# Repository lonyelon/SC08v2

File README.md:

# SC08v2: Simple Computer (8-bits, version 2)

The SC08v2 is a super-simple, **open-hardware 8bit computer** built for retro hardware enthusiasts,
for which a custom default **microcode**, **ISA**, **assembler**, **programming language (based on LISP)**, **compiler** and **operating system** are included.
The design is modular, so any of that can be replaced at any time by the user:

This repository contains various directories and files that help design, build and test both the computer's hardware and it's software. Those files and directories are the following:

| File/Dir     | Explanation                                                                             |
| ------------ | --------------------------------------------------------------------------------------- |
| `assembler/` | converts assembly code to binary data.                                                  |
| `microcode/` | files and scripts that help with designing and building the microcode for the computer. |
| `simulator/` | a complete simulator to test software in.                                               |
| `code/`      | software for the CPU.                                                                   |
| `code/so`    | complete OS.                                                                            |
| `doc/`       | documentation.                                                                          |
| `kicad/`     | KiCAD hardware designs.                                                                 |
| `drawio/`    | DrawIO diagrams.                                                                        |

## Developing software

Check the [programmer's manual](doc/programmers-manual.md) for a detailed guide on how to make software for the CPU.

## Running software in the CPU

To run software in the *simulated* CPU one has two follow two steps: compilation and execution. Let's run one of the test programs for example:

1. Compile the program by running the compiler: `python3 ./comp/compiler.py ./asm/test-programs/mult.asm`. This will result in a file named `result.bin` being created, which can be either flashed into the CPU's ROM or executed by the simulator. Note that the file has a size of exactly 64KB.
2. Run the simulator by entering the `sim` directory and then executing `cargo run ../result.bin | grep -E '^[0-9]+'`. In this case, enter a number (smaller than 255) and press enter. Repeat that step and the product of both will be outputted.

This shows that the simulator needs machine code and can not work with assembly code, since it is a one-to-one digital recreation of the real CPU.

## Contributing

Anything can be added to this repo, in whatever programming language you choose to make it, as long as it is a tool or some documentation for the SC08v2.

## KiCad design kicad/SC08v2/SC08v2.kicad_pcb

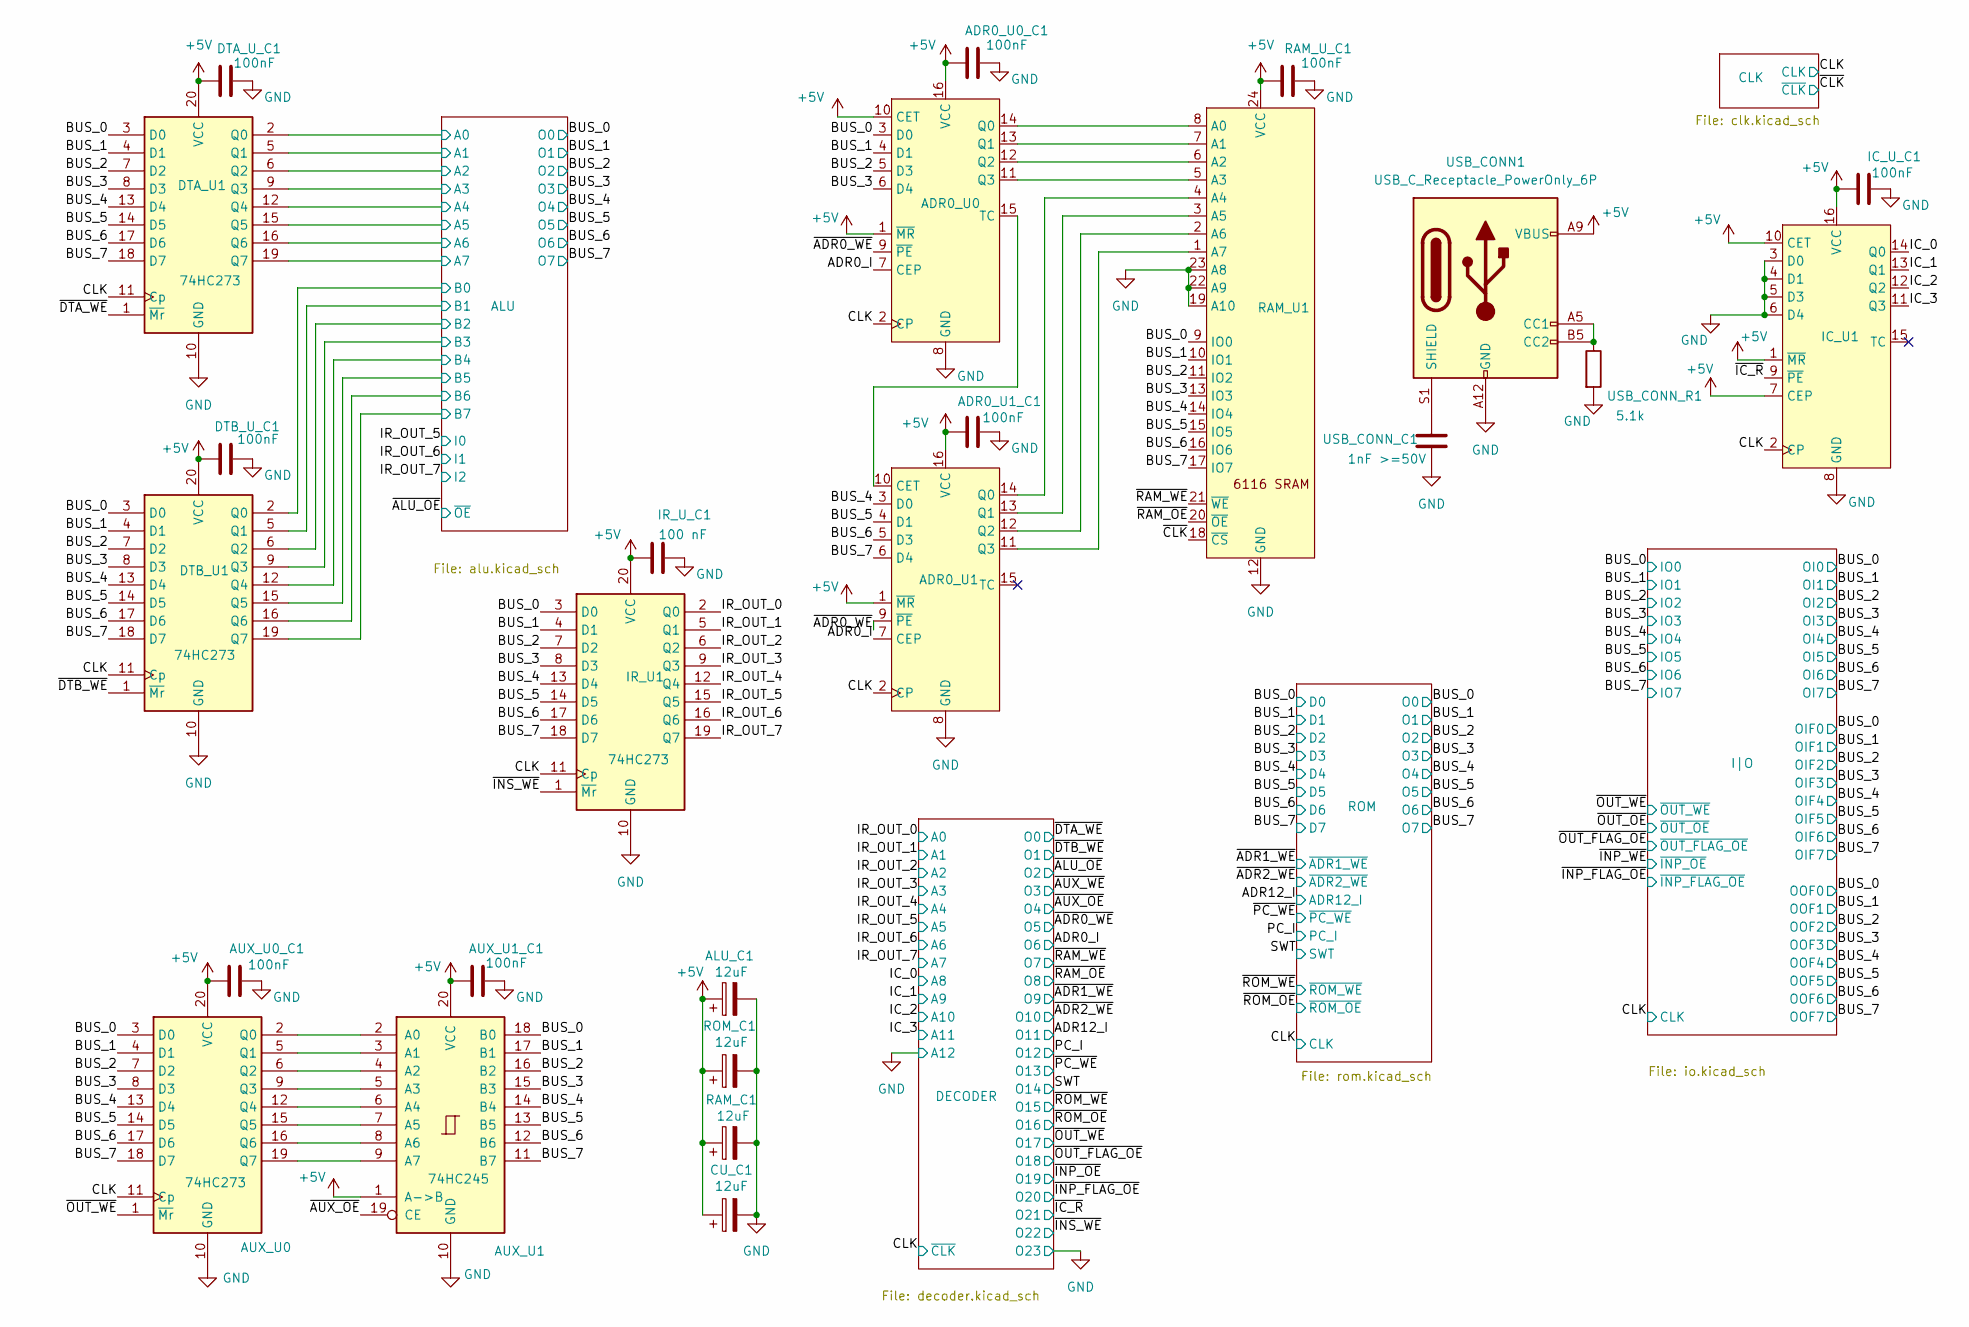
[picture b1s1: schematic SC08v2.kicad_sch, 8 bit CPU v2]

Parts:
ADR0_U0, ADR0_U1: DIP-16_W7.62mm
ADR0_U0_C1, ADR0_U1_C1: 100nF; C_Disc_D3.0mm_W1.6mm_P2.50mm
ALU_C1: 12uF; C_Radial_D5.0mm_H5.0mm_P2.00mm
AUX_U0: 74HC273; DIP-20_W7.62mm
AUX_U0_C1, AUX_U1_C1: 100nF; C_Disc_D3.0mm_W1.6mm_P2.50mm
AUX_U1: 74HC245; DIP-20_W7.62mm
CU_C1: 12uF; C_Radial_D5.0mm_H5.0mm_P2.00mm
DTA_U1: 74HC273; DIP-20_W7.62mm
DTA_U_C1: 100nF; C_Disc_D3.0mm_W1.6mm_P2.50mm
DTB_U1: 74HC273; DIP-20_W7.62mm
DTB_U_C1: 100nF; C_Disc_D3.0mm_W1.6mm_P2.50mm
IC_U1: DIP-16_W7.62mm
IC_U_C1: 100nF; C_Disc_D3.0mm_W1.6mm_P2.50mm
IR_U1: 74HC273; DIP-20_W7.62mm
IR_U_C1: 100 nF; C_Disc_D3.0mm_W1.6mm_P2.50mm
RAM_C1: 12uF; C_Radial_D5.0mm_H5.0mm_P2.00mm
RAM_U1: DIP-24_18.0mmx34.29mm_W15.24mm
RAM_U_C1: 100nF; C_Disc_D3.0mm_W1.6mm_P2.50mm
ROM_C1: 12uF; C_Radial_D5.0mm_H5.0mm_P2.00mm
USB_CONN1: USB_C_Receptacle_PowerOnly_6P; USB_C_Receptacle_GCT_USB4125-xx-x-0190_6P_TopMnt_Horizontal
USB_CONN_C1: 1nF >=50V; C_Disc_D3.0mm_W1.6mm_P2.50mm
USB_CONN_R1: 5.1k; R_Axial_DIN0204_L3.6mm_D1.6mm_P5.08mm_Horizontal

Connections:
+5V: ADR0_U0.1 (~MR), ADR0_U0.10 (CET), ADR0_U0.16 (VCC), ADR0_U0_C1.1, ADR0_U1.1 (~MR), ADR0_U1.16 (VCC), ADR0_U1_C1.1, ALU_C1.1, AUX_U0.20 (VCC), AUX_U0_C1.1, AUX_U1.1 (A->B), AUX_U1.20 (VCC), AUX_U1_C1.1, CU_C1.1, DTA_U1.20 (VCC), DTA_U_C1.1, DTB_U1.20 (VCC), DTB_U_C1.1, IC_U1.1 (~MR), IC_U1.7 (CEP), IC_U1.10 (CET), IC_U1.16 (VCC), IC_U_C1.1, IR_U1.20 (VCC), IR_U_C1.1, RAM_C1.1, RAM_U1.24 (VCC), RAM_U_C1.1, ROM_C1.1, USB_CONN1.A9 (VBUS), USB_CONN1.B9 (VBUS); also elsewhere on the board
/ADR0_I: ADR0_U0.7 (CEP), ADR0_U1.7 (CEP); also elsewhere on the board
/ALU/A0: DTA_U1.2 (Q0); also elsewhere on the board
/ALU/A1: DTA_U1.5 (Q1); also elsewhere on the board
/ALU/A2: DTA_U1.6 (Q2); also elsewhere on the board
/ALU/A3: DTA_U1.9 (Q3); also elsewhere on the board
/ALU/A4: DTA_U1.12 (Q4); also elsewhere on the board
/ALU/A5: DTA_U1.15 (Q5); also elsewhere on the board
/ALU/A6: DTA_U1.16 (Q6); also elsewhere on the board
/ALU/A7: DTA_U1.19 (Q7); also elsewhere on the board
/ALU/B0: DTB_U1.2 (Q0); also elsewhere on the board
/ALU/B1: DTB_U1.5 (Q1); also elsewhere on the board
/ALU/B2: DTB_U1.6 (Q2); also elsewhere on the board
/ALU/B3: DTB_U1.9 (Q3); also elsewhere on the board
/ALU/B4: DTB_U1.12 (Q4); also elsewhere on the board
/ALU/B5: DTB_U1.15 (Q5); also elsewhere on the board
/ALU/B6: DTB_U1.16 (Q6); also elsewhere on the board
/ALU/B7: DTB_U1.19 (Q7); also elsewhere on the board
/BUS_0: ADR0_U0.3 (D0), AUX_U0.3 (D0), AUX_U1.18 (B0), DTA_U1.3 (D0), DTB_U1.3 (D0), IR_U1.3 (D0), RAM_U1.9 (IO0); also elsewhere on the board
/BUS_1: ADR0_U0.4 (D1), AUX_U0.4 (D1), AUX_U1.17 (B1), DTA_U1.4 (D1), DTB_U1.4 (D1), IR_U1.4 (D1), RAM_U1.10 (IO1); also elsewhere on the board
/BUS_2: ADR0_U0.5 (D3), AUX_U0.7 (D2), AUX_U1.16 (B2), DTA_U1.7 (D2), DTB_U1.7 (D2), IR_U1.7 (D2), RAM_U1.11 (IO2); also elsewhere on the board
/BUS_3: ADR0_U0.6 (D4), AUX_U0.8 (D3), AUX_U1.15 (B3), DTA_U1.8 (D3), DTB_U1.8 (D3), IR_U1.8 (D3), RAM_U1.13 (IO3); also elsewhere on the board
/BUS_4: ADR0_U1.3 (D0), AUX_U0.13 (D4), AUX_U1.14 (B4), DTA_U1.13 (D4), DTB_U1.13 (D4), IR_U1.13 (D4), RAM_U1.14 (IO4); also elsewhere on the board
/BUS_5: ADR0_U1.4 (D1), AUX_U0.14 (D5), AUX_U1.13 (B5), DTA_U1.14 (D5), DTB_U1.14 (D5), IR_U1.14 (D5), RAM_U1.15 (IO5); also elsewhere on the board
/BUS_6: ADR0_U1.5 (D3), AUX_U0.17 (D6), AUX_U1.12 (B6), DTA_U1.17 (D6), DTB_U1.17 (D6), IR_U1.17 (D6), RAM_U1.16 (IO6); also elsewhere on the board
/BUS_7: ADR0_U1.6 (D4), AUX_U0.18 (D7), AUX_U1.11 (B7), DTA_U1.18 (D7), DTB_U1.18 (D7), IR_U1.18 (D7), RAM_U1.17 (IO7); also elsewhere on the board
/CLK: ADR0_U0.2 (CP), ADR0_U1.2 (CP), AUX_U0.11 (Cp), DTA_U1.11 (Cp), DTB_U1.11 (Cp), IC_U1.2 (CP), IR_U1.11 (Cp); also elsewhere on the board
/IC_0: IC_U1.14 (Q0); also elsewhere on the board
/IC_1: IC_U1.13 (Q1); also elsewhere on the board
/IC_2: IC_U1.12 (Q2); also elsewhere on the board
/IC_3: IC_U1.11 (Q3); also elsewhere on the board
/IR_OUT_0: IR_U1.2 (Q0); also elsewhere on the board
/IR_OUT_1: IR_U1.5 (Q1); also elsewhere on the board
/IR_OUT_2: IR_U1.6 (Q2); also elsewhere on the board
/IR_OUT_3: IR_U1.9 (Q3); also elsewhere on the board
/IR_OUT_4: IR_U1.12 (Q4); also elsewhere on the board
/IR_OUT_5: IR_U1.15 (Q5); also elsewhere on the board
/IR_OUT_6: IR_U1.16 (Q6); also elsewhere on the board
/IR_OUT_7: IR_U1.19 (Q7); also elsewhere on the board
/~ADR0_WE: ADR0_U0.9 (~PE), ADR0_U1.9 (~PE); also elsewhere on the board
/~AUX_OE: AUX_U1.19 (CE); also elsewhere on the board
/~CLK: RAM_U1.18 (~CS); also elsewhere on the board
/~DTA_WE: DTA_U1.1 (~Mr); also elsewhere on the board
/~DTB_WE: DTB_U1.1 (~Mr); also elsewhere on the board
/~IC_R: IC_U1.9 (~PE); also elsewhere on the board
/~INS_WE: IR_U1.1 (~Mr); also elsewhere on the board
/~OUT_WE: AUX_U0.1 (~Mr); also elsewhere on the board
/~RAM_OE: RAM_U1.20 (~OE); also elsewhere on the board
/~RAM_WE: RAM_U1.21 (~WE); also elsewhere on the board
GND: ADR0_U0.8 (GND), ADR0_U0_C1.2, ADR0_U1.8 (GND), ADR0_U1_C1.2, ALU_C1.2, AUX_U0.10 (GND), AUX_U0_C1.2, AUX_U1.10 (GND), AUX_U1_C1.2, CU_C1.2, DTA_U1.10 (GND), DTA_U_C1.2, DTB_U1.10 (GND), DTB_U_C1.2, IC_U1.3 (D0), IC_U1.4 (D1), IC_U1.5 (D3), IC_U1.6 (D4), IC_U1.8 (GND), IC_U_C1.2, IR_U1.10 (GND), IR_U_C1.2, RAM_C1.2, RAM_U1.12 (GND), RAM_U1.19 (A10), RAM_U1.22 (A9), RAM_U1.23 (A8), RAM_U_C1.2, ROM_C1.2, USB_CONN1.A12 (GND), USB_CONN1.B12 (GND), USB_CONN_C1.2, USB_CONN_R1.2; also elsewhere on the board
unnamed: ADR0_U0.14 (Q0), RAM_U1.8 (A0)
unnamed: ADR0_U0.13 (Q1), RAM_U1.7 (A1)
unnamed: ADR0_U0.12 (Q2), RAM_U1.6 (A2)
unnamed: ADR0_U0.11 (Q3), RAM_U1.5 (A3)
unnamed: ADR0_U0.15 (TC), ADR0_U1.10 (CET)
unnamed: ADR0_U1.14 (Q0), RAM_U1.4 (A4)
unnamed: ADR0_U1.13 (Q1), RAM_U1.3 (A5)
unnamed: ADR0_U1.12 (Q2), RAM_U1.2 (A6)
unnamed: ADR0_U1.11 (Q3), RAM_U1.1 (A7)
unnamed: AUX_U0.2 (Q0), AUX_U1.2 (A0)
unnamed: AUX_U0.5 (Q1), AUX_U1.3 (A1)
unnamed: AUX_U0.6 (Q2), AUX_U1.4 (A2)
unnamed: AUX_U0.9 (Q3), AUX_U1.5 (A3)
unnamed: AUX_U0.12 (Q4), AUX_U1.6 (A4)
unnamed: AUX_U0.15 (Q5), AUX_U1.7 (A5)
unnamed: AUX_U0.16 (Q6), AUX_U1.8 (A6)
unnamed: AUX_U0.19 (Q7), AUX_U1.9 (A7)
unnamed: USB_CONN1.A5 (CC1), USB_CONN1.B5 (CC2), USB_CONN_R1.1
unnamed: USB_CONN1.S1 (SHIELD), USB_CONN_C1.1

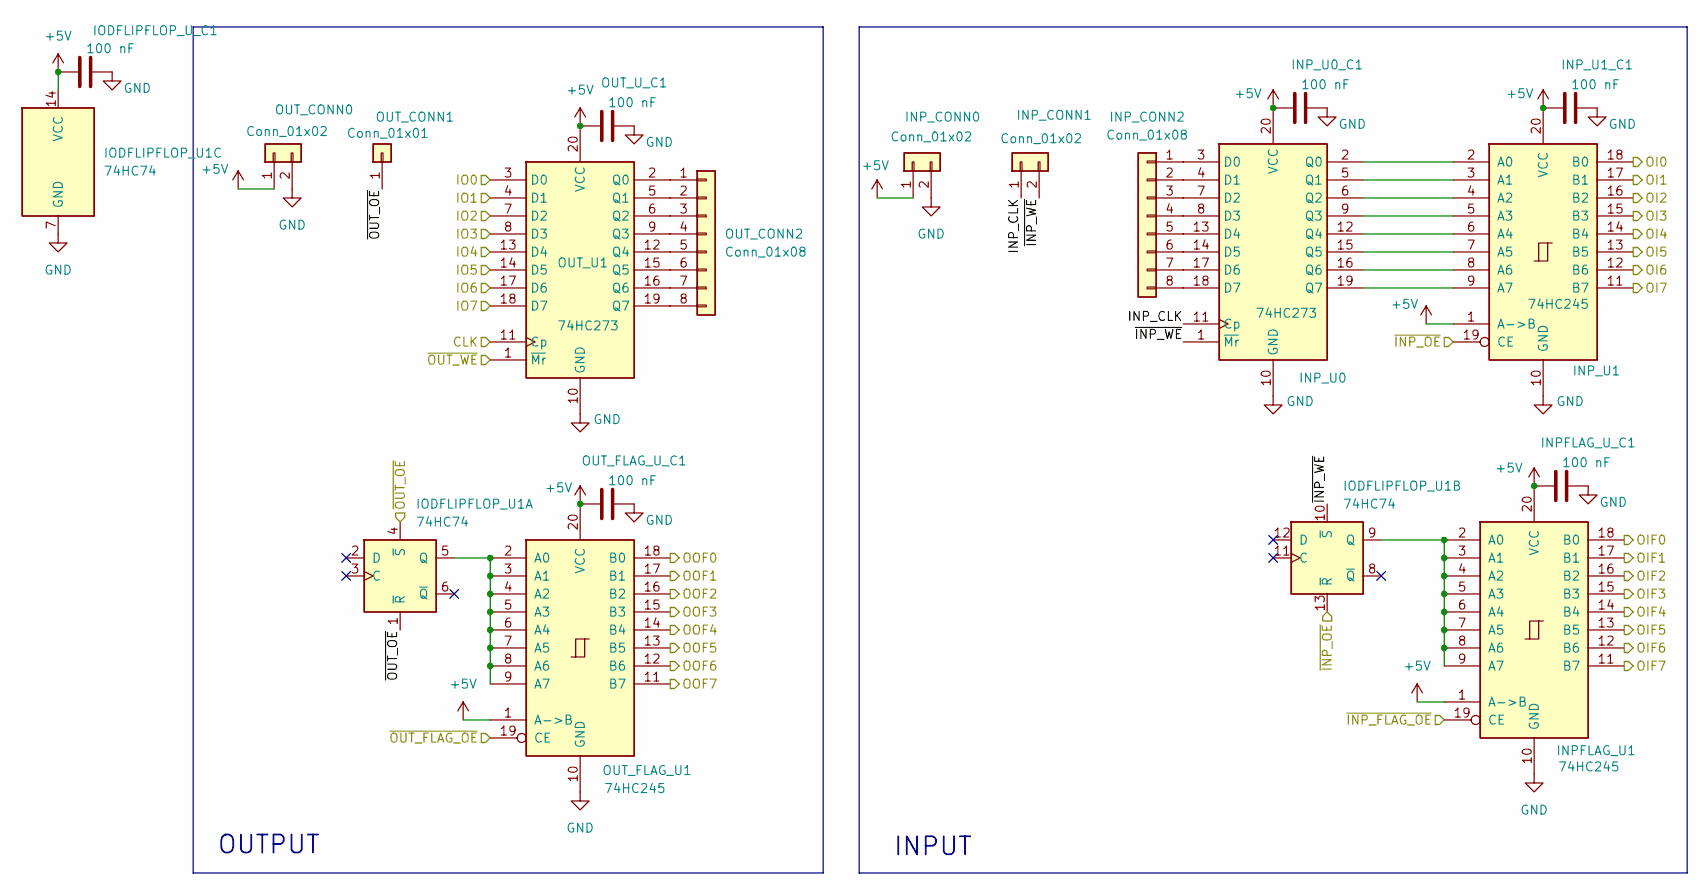
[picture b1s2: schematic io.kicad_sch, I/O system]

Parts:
INPFLAG_U1: 74HC245; DIP-20_W7.62mm
INPFLAG_U_C1: 100 nF; C_Disc_D3.0mm_W1.6mm_P2.50mm
INP_CONN0, INP_CONN1: Conn_01x02; PinHeader_1x02_P2.54mm_Vertical
INP_CONN2: Conn_01x08; PinHeader_1x08_P2.54mm_Vertical
INP_U0: 74HC273; DIP-20_W7.62mm
INP_U0_C1, INP_U1_C1: 100 nF; C_Disc_D3.0mm_W1.6mm_P2.50mm
INP_U1: 74HC245; DIP-20_W7.62mm
IODFLIPFLOP_U1: 74HC74; DIP-14_W7.62mm
IODFLIPFLOP_U_C1: 100 nF; C_Disc_D3.0mm_W1.6mm_P2.50mm
OUT_CONN0: Conn_01x02; PinHeader_1x02_P2.54mm_Vertical
OUT_CONN1: Conn_01x01; PinHeader_1x01_P2.54mm_Vertical
OUT_CONN2: Conn_01x08; PinHeader_1x08_P2.54mm_Vertical
OUT_FLAG_U1: 74HC245; DIP-20_W7.62mm
OUT_FLAG_U_C1: 100 nF; C_Disc_D3.0mm_W1.6mm_P2.50mm
OUT_U1: 74HC273; DIP-20_W7.62mm
OUT_U_C1: 100 nF; C_Disc_D3.0mm_W1.6mm_P2.50mm

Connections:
+5V: INPFLAG_U1.1 (A->B), INPFLAG_U1.20 (VCC), INPFLAG_U_C1.1, INP_CONN0.1, INP_U0.20 (VCC), INP_U0_C1.1, INP_U1.1 (A->B), INP_U1.20 (VCC), INP_U1_C1.1, IODFLIPFLOP_U1.14 (VCC), IODFLIPFLOP_U_C1.1, OUT_CONN0.1, OUT_FLAG_U1.1 (A->B), OUT_FLAG_U1.20 (VCC), OUT_FLAG_U_C1.1, OUT_U1.20 (VCC), OUT_U_C1.1; also elsewhere on the board
/BUS_0: INPFLAG_U1.18 (B0), INP_U1.18 (B0), OUT_FLAG_U1.18 (B0), OUT_U1.3 (D0); also elsewhere on the board
/BUS_1: INPFLAG_U1.17 (B1), INP_U1.17 (B1), OUT_FLAG_U1.17 (B1), OUT_U1.4 (D1); also elsewhere on the board
/BUS_2: INPFLAG_U1.16 (B2), INP_U1.16 (B2), OUT_FLAG_U1.16 (B2), OUT_U1.7 (D2); also elsewhere on the board
/BUS_3: INPFLAG_U1.15 (B3), INP_U1.15 (B3), OUT_FLAG_U1.15 (B3), OUT_U1.8 (D3); also elsewhere on the board
/BUS_4: INPFLAG_U1.14 (B4), INP_U1.14 (B4), OUT_FLAG_U1.14 (B4), OUT_U1.13 (D4); also elsewhere on the board
/BUS_5: INPFLAG_U1.13 (B5), INP_U1.13 (B5), OUT_FLAG_U1.13 (B5), OUT_U1.14 (D5); also elsewhere on the board
/BUS_6: INPFLAG_U1.12 (B6), INP_U1.12 (B6), OUT_FLAG_U1.12 (B6), OUT_U1.17 (D6); also elsewhere on the board
/BUS_7: INPFLAG_U1.11 (B7), INP_U1.11 (B7), OUT_FLAG_U1.11 (B7), OUT_U1.18 (D7); also elsewhere on the board
/CLK: OUT_U1.11 (Cp); also elsewhere on the board
/I|O/INP_CLK: INP_CONN1.1, INP_U0.11 (Cp)
/I|O/~INP_WE: INP_CONN1.2, INP_U0.1 (~Mr), IODFLIPFLOP_U1.10 (~S)
/~INP_FLAG_OE: INPFLAG_U1.19 (CE); also elsewhere on the board
/~INP_WE: INP_U1.19 (CE), IODFLIPFLOP_U1.13 (~R)
/~OUT_FLAG_OE: OUT_FLAG_U1.19 (CE); also elsewhere on the board
/~OUT_OE: IODFLIPFLOP_U1.1 (~R), IODFLIPFLOP_U1.4 (~S), OUT_CONN1.1 (Pin_1_1)
/~OUT_WE: OUT_U1.1 (~Mr); also elsewhere on the board
GND: INPFLAG_U1.10 (GND), INPFLAG_U_C1.2, INP_CONN0.2, INP_U0.10 (GND), INP_U0_C1.2, INP_U1.10 (GND), INP_U1_C1.2, IODFLIPFLOP_U1.7 (GND), IODFLIPFLOP_U_C1.2, OUT_CONN0.2, OUT_FLAG_U1.10 (GND), OUT_FLAG_U_C1.2, OUT_U1.10 (GND), OUT_U_C1.2; also elsewhere on the board
unnamed: INPFLAG_U1.2 (A0), INPFLAG_U1.3 (A1), INPFLAG_U1.4 (A2), INPFLAG_U1.5 (A3), INPFLAG_U1.6 (A4), INPFLAG_U1.7 (A5), INPFLAG_U1.8 (A6), INPFLAG_U1.9 (A7), IODFLIPFLOP_U1.9 (Q)
unnamed: INP_CONN2.1, INP_U0.3 (D0)
unnamed: INP_CONN2.2, INP_U0.4 (D1)
unnamed: INP_CONN2.3, INP_U0.7 (D2)
unnamed: INP_CONN2.4, INP_U0.8 (D3)
unnamed: INP_CONN2.5, INP_U0.13 (D4)
unnamed: INP_CONN2.6, INP_U0.14 (D5)
unnamed: INP_CONN2.7, INP_U0.17 (D6)
unnamed: INP_CONN2.8, INP_U0.18 (D7)
unnamed: INP_U0.2 (Q0), INP_U1.2 (A0)
unnamed: INP_U0.5 (Q1), INP_U1.3 (A1)
unnamed: INP_U0.6 (Q2), INP_U1.4 (A2)
unnamed: INP_U0.9 (Q3), INP_U1.5 (A3)
unnamed: INP_U0.12 (Q4), INP_U1.6 (A4)
unnamed: INP_U0.15 (Q5), INP_U1.7 (A5)
unnamed: INP_U0.16 (Q6), INP_U1.8 (A6)
unnamed: INP_U0.19 (Q7), INP_U1.9 (A7)
unnamed: IODFLIPFLOP_U1.5 (Q), OUT_FLAG_U1.2 (A0), OUT_FLAG_U1.3 (A1), OUT_FLAG_U1.4 (A2), OUT_FLAG_U1.5 (A3), OUT_FLAG_U1.6 (A4), OUT_FLAG_U1.7 (A5), OUT_FLAG_U1.8 (A6), OUT_FLAG_U1.9 (A7)
unnamed: OUT_CONN2.1, OUT_U1.2 (Q0)
unnamed: OUT_CONN2.2, OUT_U1.5 (Q1)
unnamed: OUT_CONN2.3, OUT_U1.6 (Q2)
unnamed: OUT_CONN2.4, OUT_U1.9 (Q3)
unnamed: OUT_CONN2.5, OUT_U1.12 (Q4)
unnamed: OUT_CONN2.6, OUT_U1.15 (Q5)
unnamed: OUT_CONN2.7, OUT_U1.16 (Q6)
unnamed: OUT_CONN2.8, OUT_U1.19 (Q7)

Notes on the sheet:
INPUT
OUTPUT

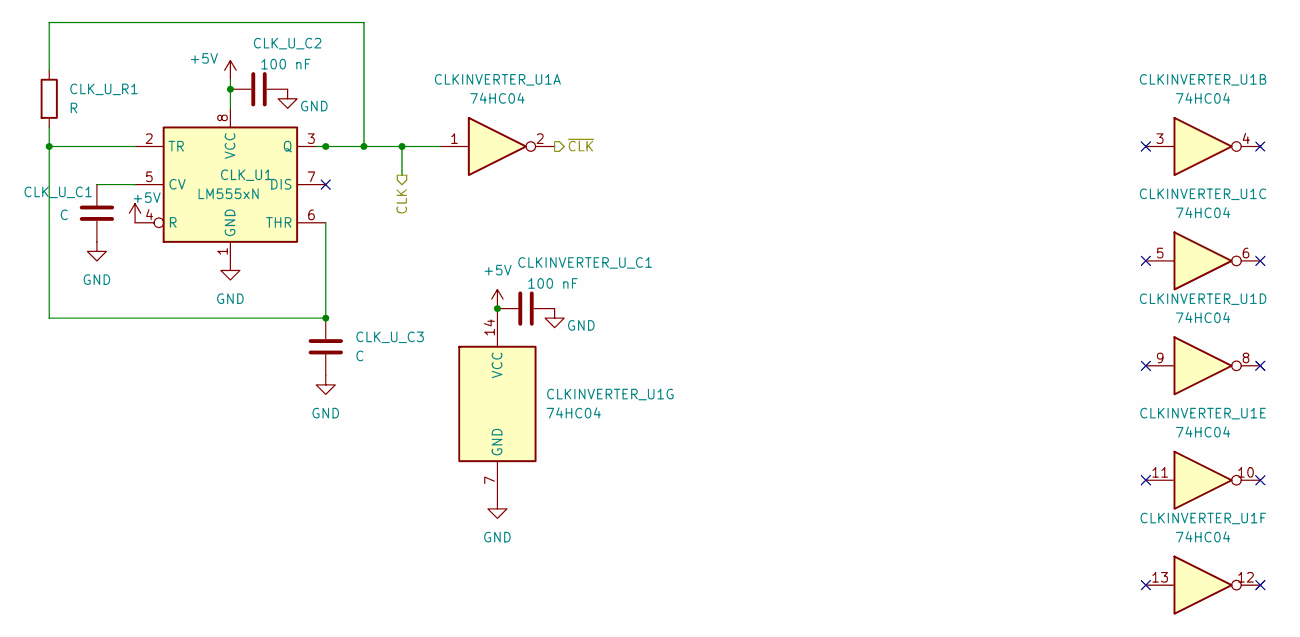
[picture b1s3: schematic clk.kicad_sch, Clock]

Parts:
CLKINVERTER_U1: 74HC04; DIP-14_W7.62mm
CLKINVERTER_U_C1: 100 nF; C_Disc_D3.0mm_W1.6mm_P2.50mm
CLK_U1: LM555xN; DIP-8_W7.62mm
CLK_U_C1, CLK_U_C3: C; C_Disc_D3.0mm_W1.6mm_P2.50mm
CLK_U_C2: 100 nF; C_Disc_D3.0mm_W1.6mm_P2.50mm
CLK_U_R1: R; R_Axial_DIN0204_L3.6mm_D1.6mm_P5.08mm_Horizontal

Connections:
+5V: CLKINVERTER_U1.14 (VCC), CLKINVERTER_U_C1.1, CLK_U1.4 (R), CLK_U1.8 (VCC), CLK_U_C2.1; also elsewhere on the board
/CLK: CLKINVERTER_U1.1, CLK_U1.3 (Q), CLK_U_R1.1; also elsewhere on the board
/~CLK: CLKINVERTER_U1.2; also elsewhere on the board
GND: CLKINVERTER_U1.7 (GND), CLKINVERTER_U_C1.2, CLK_U1.1 (GND), CLK_U_C1.2, CLK_U_C2.2, CLK_U_C3.2; also elsewhere on the board
unnamed: CLK_U1.5 (CV), CLK_U_C1.1
unnamed: CLK_U1.2 (TR), CLK_U1.6 (THR), CLK_U_C3.1, CLK_U_R1.2

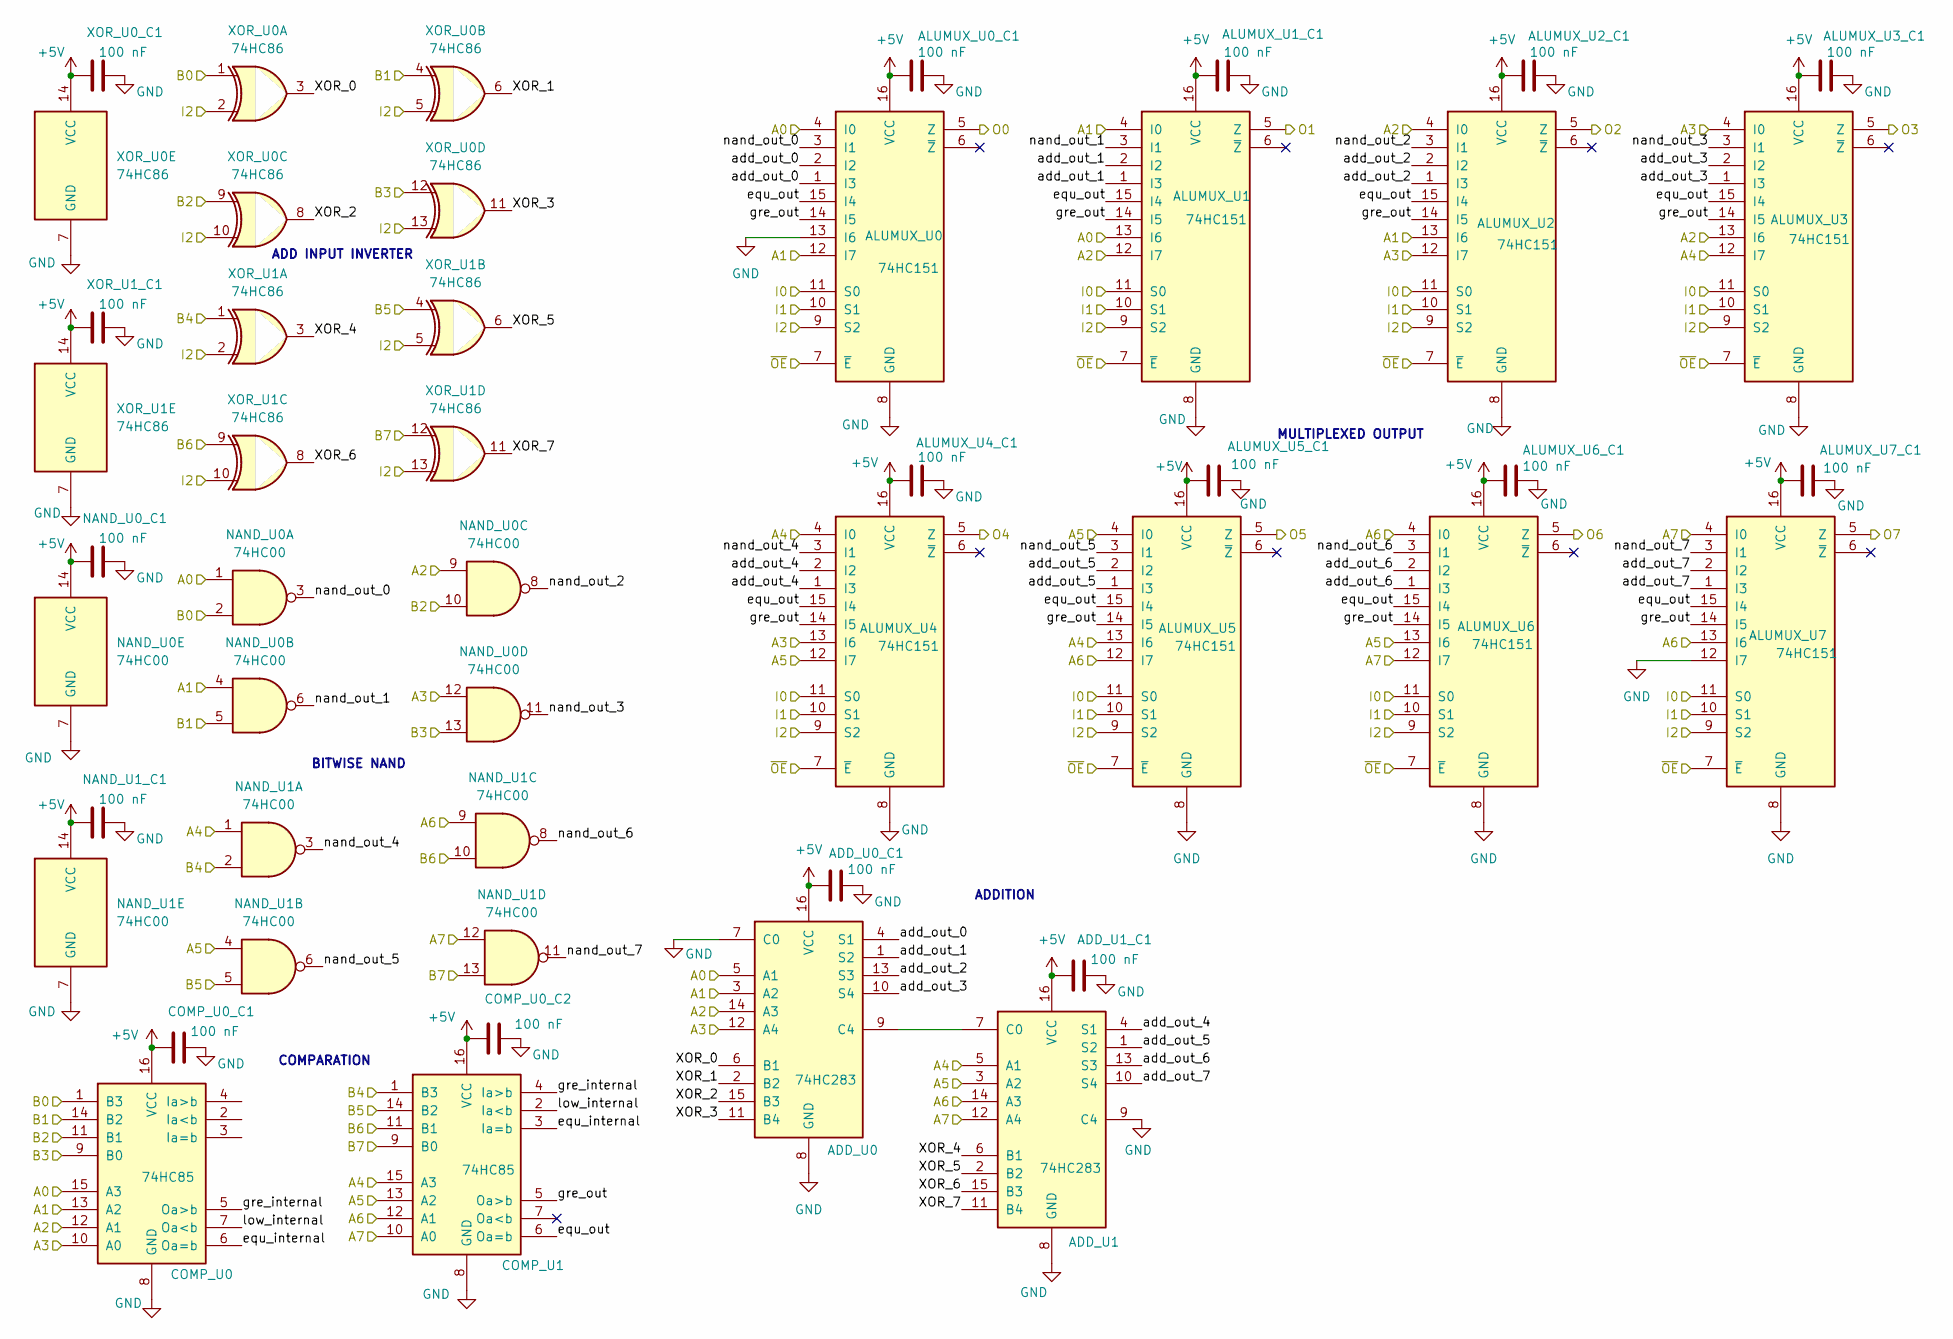
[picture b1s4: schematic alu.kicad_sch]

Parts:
ADD_U0, ADD_U1: 74HC283; DIP-16_W7.62mm
ADD_U0_C1, ADD_U1_C1: 100 nF; C_Disc_D3.0mm_W1.6mm_P2.50mm
ALUMUX_U0, ALUMUX_U1, ALUMUX_U2, ALUMUX_U3, ALUMUX_U4, ALUMUX_U5, ALUMUX_U6, ALUMUX_U7: 74HC151; DIP-16_W7.62mm
ALUMUX_U0_C1, ALUMUX_U1_C1, ALUMUX_U2_C1, ALUMUX_U3_C1, ALUMUX_U4_C1, ALUMUX_U5_C1, ALUMUX_U6_C1, ALUMUX_U7_C1: 100 nF; C_Disc_D3.0mm_W1.6mm_P2.50mm
COMP_U0, COMP_U1: 74HC85; DIP-16_W7.62mm
COMP_U0_C1, COMP_U0_C2: 100 nF; C_Disc_D3.0mm_W1.6mm_P2.50mm
NAND_U0, NAND_U1: 74HC00; DIP-14_W7.62mm
NAND_U0_C1, NAND_U1_C1: 100 nF; C_Disc_D3.0mm_W1.6mm_P2.50mm
XOR_U0, XOR_U1: 74HC86; DIP-14_W7.62mm
XOR_U0_C1, XOR_U1_C1: 100 nF; C_Disc_D3.0mm_W1.6mm_P2.50mm

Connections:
+5V: ADD_U0.16 (VCC), ADD_U0_C1.1, ADD_U1.16 (VCC), ADD_U1_C1.1, ALUMUX_U0.16 (VCC), ALUMUX_U0_C1.1, ALUMUX_U1.16 (VCC), ALUMUX_U1_C1.1, ALUMUX_U2.16 (VCC), ALUMUX_U2_C1.1, ALUMUX_U3.16 (VCC), ALUMUX_U3_C1.1, ALUMUX_U4.16 (VCC), ALUMUX_U4_C1.1, ALUMUX_U5.16 (VCC), ALUMUX_U5_C1.1, ALUMUX_U6.16 (VCC), ALUMUX_U6_C1.1, ALUMUX_U7.16 (VCC), ALUMUX_U7_C1.1, COMP_U0.16 (VCC), COMP_U0_C1.1, COMP_U0_C2.1, COMP_U1.16 (VCC), NAND_U0.14 (VCC), NAND_U0_C1.1, NAND_U1.14 (VCC), NAND_U1_C1.1, XOR_U0.14 (VCC), XOR_U0_C1.1, XOR_U1.14 (VCC), XOR_U1_C1.1; also elsewhere on the board
/ALU/A0: ADD_U0.5 (A1), ALUMUX_U0.4 (I0), ALUMUX_U1.13 (I6), COMP_U0.15 (A3), NAND_U0.1; also elsewhere on the board
/ALU/A1: ADD_U0.3 (A2), ALUMUX_U0.12 (I7), ALUMUX_U1.4 (I0), ALUMUX_U2.13 (I6), COMP_U0.13 (A2), NAND_U0.4; also elsewhere on the board
/ALU/A2: ADD_U0.14 (A3), ALUMUX_U1.12 (I7), ALUMUX_U2.4 (I0), ALUMUX_U3.13 (I6), COMP_U0.12 (A1), NAND_U0.9; also elsewhere on the board
/ALU/A3: ADD_U0.12 (A4), ALUMUX_U2.12 (I7), ALUMUX_U3.4 (I0), ALUMUX_U4.13 (I6), COMP_U0.10 (A0), NAND_U0.12; also elsewhere on the board
/ALU/A4: ADD_U1.5 (A1), ALUMUX_U3.12 (I7), ALUMUX_U4.4 (I0), ALUMUX_U5.13 (I6), COMP_U1.15 (A3), NAND_U1.1; also elsewhere on the board
/ALU/A5: ADD_U1.3 (A2), ALUMUX_U4.12 (I7), ALUMUX_U5.4 (I0), ALUMUX_U6.13 (I6), COMP_U1.13 (A2), NAND_U1.4; also elsewhere on the board
/ALU/A6: ADD_U1.14 (A3), ALUMUX_U5.12 (I7), ALUMUX_U6.4 (I0), ALUMUX_U7.13 (I6), COMP_U1.12 (A1), NAND_U1.9; also elsewhere on the board
/ALU/A7: ADD_U1.12 (A4), ALUMUX_U6.12 (I7), ALUMUX_U7.4 (I0), COMP_U1.10 (A0), NAND_U1.12; also elsewhere on the board
/ALU/B0: COMP_U0.1 (B3), NAND_U0.2, XOR_U0.1; also elsewhere on the board
/ALU/B1: COMP_U0.14 (B2), NAND_U0.5, XOR_U0.4; also elsewhere on the board
/ALU/B2: COMP_U0.11 (B1), NAND_U0.10, XOR_U0.9; also elsewhere on the board
/ALU/B3: COMP_U0.9 (B0), NAND_U0.13, XOR_U0.12; also elsewhere on the board
/ALU/B4: COMP_U1.1 (B3), NAND_U1.2, XOR_U1.1; also elsewhere on the board
/ALU/B5: COMP_U1.14 (B2), NAND_U1.5, XOR_U1.4; also elsewhere on the board
/ALU/B6: COMP_U1.11 (B1), NAND_U1.10, XOR_U1.9; also elsewhere on the board
/ALU/B7: COMP_U1.9 (B0), NAND_U1.13, XOR_U1.12; also elsewhere on the board
/ALU/XOR_0: ADD_U0.6 (B1), XOR_U0.3
/ALU/XOR_1: ADD_U0.2 (B2), XOR_U0.6
/ALU/XOR_2: ADD_U0.15 (B3), XOR_U0.8
/ALU/XOR_3: ADD_U0.11 (B4), XOR_U0.11
/ALU/XOR_4: ADD_U1.6 (B1), XOR_U1.3
/ALU/XOR_5: ADD_U1.2 (B2), XOR_U1.6
/ALU/XOR_6: ADD_U1.15 (B3), XOR_U1.8
/ALU/XOR_7: ADD_U1.11 (B4), XOR_U1.11
/ALU/add_out_0: ADD_U0.4 (S1), ALUMUX_U0.1 (I3), ALUMUX_U0.2 (I2)
/ALU/add_out_1: ADD_U0.1 (S2), ALUMUX_U1.1 (I3), ALUMUX_U1.2 (I2)
/ALU/add_out_2: ADD_U0.13 (S3), ALUMUX_U2.1 (I3), ALUMUX_U2.2 (I2)
/ALU/add_out_3: ADD_U0.10 (S4), ALUMUX_U3.1 (I3), ALUMUX_U3.2 (I2)
/ALU/add_out_4: ADD_U1.4 (S1), ALUMUX_U4.1 (I3), ALUMUX_U4.2 (I2)
/ALU/add_out_5: ADD_U1.1 (S2), ALUMUX_U5.1 (I3), ALUMUX_U5.2 (I2)
/ALU/add_out_6: ADD_U1.13 (S3), ALUMUX_U6.1 (I3), ALUMUX_U6.2 (I2)
/ALU/add_out_7: ADD_U1.10 (S4), ALUMUX_U7.1 (I3), ALUMUX_U7.2 (I2)
/ALU/equ_internal: COMP_U0.6 (Oa=b), COMP_U1.3 (Ia=b)
/ALU/equ_out: ALUMUX_U0.15 (I4), ALUMUX_U1.15 (I4), ALUMUX_U2.15 (I4), ALUMUX_U3.15 (I4), ALUMUX_U4.15 (I4), ALUMUX_U5.15 (I4), ALUMUX_U6.15 (I4), ALUMUX_U7.15 (I4), COMP_U1.6 (Oa=b)
/ALU/gre_internal: COMP_U0.5 (Oa>b), COMP_U1.4 (Ia>b)
/ALU/gre_out: ALUMUX_U0.14 (I5), ALUMUX_U1.14 (I5), ALUMUX_U2.14 (I5), ALUMUX_U3.14 (I5), ALUMUX_U4.14 (I5), ALUMUX_U5.14 (I5), ALUMUX_U6.14 (I5), ALUMUX_U7.14 (I5), COMP_U1.5 (Oa>b)
/ALU/low_internal: COMP_U0.7 (Oa<b), COMP_U1.2 (Ia<b)
/ALU/nand_out_0: ALUMUX_U0.3 (I1), NAND_U0.3
/ALU/nand_out_1: ALUMUX_U1.3 (I1), NAND_U0.6
/ALU/nand_out_2: ALUMUX_U2.3 (I1), NAND_U0.8
/ALU/nand_out_3: ALUMUX_U3.3 (I1), NAND_U0.11
/ALU/nand_out_4: ALUMUX_U4.3 (I1), NAND_U1.3
/ALU/nand_out_5: ALUMUX_U5.3 (I1), NAND_U1.6
/ALU/nand_out_6: ALUMUX_U6.3 (I1), NAND_U1.8
/ALU/nand_out_7: ALUMUX_U7.3 (I1), NAND_U1.11
/BUS_0: ALUMUX_U0.5 (Z); also elsewhere on the board
/BUS_1: ALUMUX_U1.5 (Z); also elsewhere on the board
/BUS_2: ALUMUX_U2.5 (Z); also elsewhere on the board
/BUS_3: ALUMUX_U3.5 (Z); also elsewhere on the board
/BUS_4: ALUMUX_U4.5 (Z); also elsewhere on the board
/BUS_5: ALUMUX_U5.5 (Z); also elsewhere on the board
/BUS_6: ALUMUX_U6.5 (Z); also elsewhere on the board
/BUS_7: ALUMUX_U7.5 (Z); also elsewhere on the board
/IR_OUT_5: ALUMUX_U0.11 (S0), ALUMUX_U1.11 (S0), ALUMUX_U2.11 (S0), ALUMUX_U3.11 (S0), ALUMUX_U4.11 (S0), ALUMUX_U5.11 (S0), ALUMUX_U6.11 (S0), ALUMUX_U7.11 (S0); also elsewhere on the board
/IR_OUT_6: ALUMUX_U0.10 (S1), ALUMUX_U1.10 (S1), ALUMUX_U2.10 (S1), ALUMUX_U3.10 (S1), ALUMUX_U4.10 (S1), ALUMUX_U5.10 (S1), ALUMUX_U6.10 (S1), ALUMUX_U7.10 (S1); also elsewhere on the board
/IR_OUT_7: ALUMUX_U0.9 (S2), ALUMUX_U1.9 (S2), ALUMUX_U2.9 (S2), ALUMUX_U3.9 (S2), ALUMUX_U4.9 (S2), ALUMUX_U5.9 (S2), ALUMUX_U6.9 (S2), ALUMUX_U7.9 (S2), XOR_U0.2, XOR_U0.5, XOR_U0.10, XOR_U0.13, XOR_U1.2, XOR_U1.5, XOR_U1.10, XOR_U1.13; also elsewhere on the board
/~ALU_OE: ALUMUX_U0.7 (~E), ALUMUX_U1.7 (~E), ALUMUX_U2.7 (~E), ALUMUX_U3.7 (~E), ALUMUX_U4.7 (~E), ALUMUX_U5.7 (~E), ALUMUX_U6.7 (~E), ALUMUX_U7.7 (~E); also elsewhere on the board
GND: ADD_U0.7 (C0), ADD_U0.8 (GND), ADD_U0_C1.2, ADD_U1.8 (GND), ADD_U1.9 (C4), ADD_U1_C1.2, ALUMUX_U0.8 (GND), ALUMUX_U0.13 (I6), ALUMUX_U0_C1.2, ALUMUX_U1.8 (GND), ALUMUX_U1_C1.2, ALUMUX_U2.8 (GND), ALUMUX_U2_C1.2, ALUMUX_U3.8 (GND), ALUMUX_U3_C1.2, ALUMUX_U4.8 (GND), ALUMUX_U4_C1.2, ALUMUX_U5.8 (GND), ALUMUX_U5_C1.2, ALUMUX_U6.8 (GND), ALUMUX_U6_C1.2, ALUMUX_U7.8 (GND), ALUMUX_U7.12 (I7), ALUMUX_U7_C1.2, COMP_U0.8 (GND), COMP_U0_C1.2, COMP_U0_C2.2, COMP_U1.8 (GND), NAND_U0.7 (GND), NAND_U0_C1.2, NAND_U1.7 (GND), NAND_U1_C1.2, XOR_U0.7 (GND), XOR_U0_C1.2, XOR_U1.7 (GND), XOR_U1_C1.2; also elsewhere on the board
unnamed: ADD_U0.9 (C4), ADD_U1.7 (C0)

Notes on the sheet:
BITWISE NAND
MULTIPLEXED OUTPUT
COMPARATION
ADDITION
ADD INPUT INVERTER

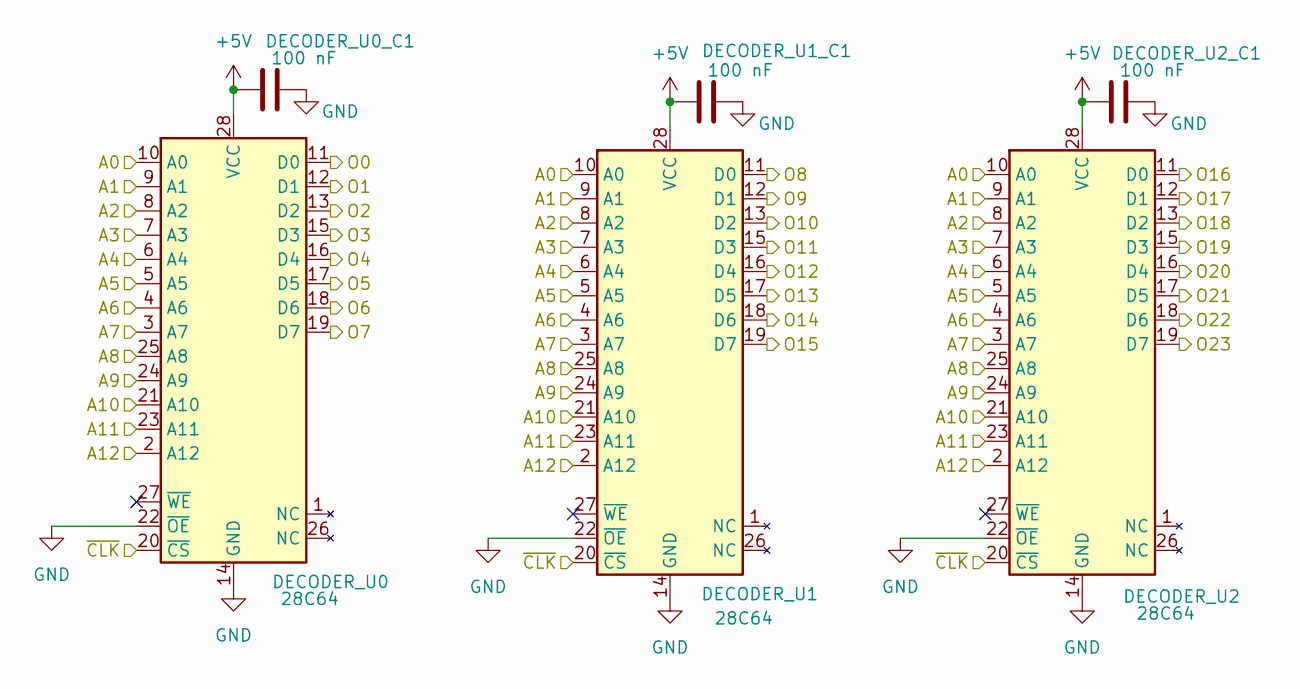
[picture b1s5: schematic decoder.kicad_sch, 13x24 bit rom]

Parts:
DECODER_U0, DECODER_U1, DECODER_U2: 28C64; DIP-28_W15.24mm
DECODER_U0_C1, DECODER_U1_C1, DECODER_U2_C1: 100 nF; C_Disc_D3.0mm_W1.6mm_P2.50mm

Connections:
+5V: DECODER_U0.28 (VCC), DECODER_U0_C1.1, DECODER_U1.28 (VCC), DECODER_U1_C1.1, DECODER_U2.28 (VCC), DECODER_U2_C1.1; also elsewhere on the board
/ADR0_I: DECODER_U0.18 (D6); also elsewhere on the board
/ADR12_I: DECODER_U1.15 (D3); also elsewhere on the board
/CLK: DECODER_U0.20 (~CS), DECODER_U1.20 (~CS), DECODER_U2.20 (~CS); also elsewhere on the board
/IC_0: DECODER_U0.25 (A8), DECODER_U1.25 (A8), DECODER_U2.25 (A8); also elsewhere on the board
/IC_1: DECODER_U0.24 (A9), DECODER_U1.24 (A9), DECODER_U2.24 (A9); also elsewhere on the board
/IC_2: DECODER_U0.21 (A10), DECODER_U1.21 (A10), DECODER_U2.21 (A10); also elsewhere on the board
/IC_3: DECODER_U0.23 (A11), DECODER_U1.23 (A11), DECODER_U2.23 (A11); also elsewhere on the board
/IR_OUT_0: DECODER_U0.10 (A0), DECODER_U1.10 (A0), DECODER_U2.10 (A0); also elsewhere on the board
/IR_OUT_1: DECODER_U0.9 (A1), DECODER_U1.9 (A1), DECODER_U2.9 (A1); also elsewhere on the board
/IR_OUT_2: DECODER_U0.8 (A2), DECODER_U1.8 (A2), DECODER_U2.8 (A2); also elsewhere on the board
/IR_OUT_3: DECODER_U0.7 (A3), DECODER_U1.7 (A3), DECODER_U2.7 (A3); also elsewhere on the board
/IR_OUT_4: DECODER_U0.6 (A4), DECODER_U1.6 (A4), DECODER_U2.6 (A4); also elsewhere on the board
/IR_OUT_5: DECODER_U0.5 (A5), DECODER_U1.5 (A5), DECODER_U2.5 (A5); also elsewhere on the board
/IR_OUT_6: DECODER_U0.4 (A6), DECODER_U1.4 (A6), DECODER_U2.4 (A6); also elsewhere on the board
/IR_OUT_7: DECODER_U0.3 (A7), DECODER_U1.3 (A7), DECODER_U2.3 (A7); also elsewhere on the board
/PC_I: DECODER_U1.16 (D4); also elsewhere on the board
/SWT: DECODER_U1.18 (D6); also elsewhere on the board
/~ADR0_WE: DECODER_U0.17 (D5); also elsewhere on the board
/~ADR1_WE: DECODER_U1.12 (D1); also elsewhere on the board
/~ADR2_WE: DECODER_U1.13 (D2); also elsewhere on the board
/~ALU_OE: DECODER_U0.13 (D2); also elsewhere on the board
/~AUX_OE: DECODER_U0.16 (D4); also elsewhere on the board
/~AUX_WE: DECODER_U0.15 (D3)
/~DTA_WE: DECODER_U0.11 (D0); also elsewhere on the board
/~DTB_WE: DECODER_U0.12 (D1); also elsewhere on the board
/~IC_R: DECODER_U2.17 (D5); also elsewhere on the board
/~INP_FLAG_OE: DECODER_U2.16 (D4); also elsewhere on the board
/~INP_OE: DECODER_U2.15 (D3)
/~INS_WE: DECODER_U2.18 (D6); also elsewhere on the board
/~OUT_FLAG_OE: DECODER_U2.13 (D2); also elsewhere on the board
/~OUT_WE: DECODER_U2.12 (D1); also elsewhere on the board
/~PC_WE: DECODER_U1.17 (D5); also elsewhere on the board
/~RAM_OE: DECODER_U1.11 (D0); also elsewhere on the board
/~RAM_WE: DECODER_U0.19 (D7); also elsewhere on the board
/~ROM_OE: DECODER_U2.11 (D0); also elsewhere on the board
/~ROM_WE: DECODER_U1.19 (D7); also elsewhere on the board
GND: DECODER_U0.2 (A12), DECODER_U0.14 (GND), DECODER_U0.22 (~OE), DECODER_U0_C1.2, DECODER_U1.2 (A12), DECODER_U1.14 (GND), DECODER_U1.22 (~OE), DECODER_U1_C1.2, DECODER_U2.2 (A12), DECODER_U2.14 (GND), DECODER_U2.19 (D7), DECODER_U2.22 (~OE), DECODER_U2_C1.2; also elsewhere on the board
